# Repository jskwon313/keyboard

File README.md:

# keyboard
This project consists of files that have been used in order to design a keyboard pcb that can be used with mechancial keyboard switches.

The following resources were used:

1) https://github.com/ruiqimao/keyboard-pcb-guide
2) https://i.imgur.com/LQXco3J.png
3) http://www.issi.com/WW/pdf/31FL3731.pdf

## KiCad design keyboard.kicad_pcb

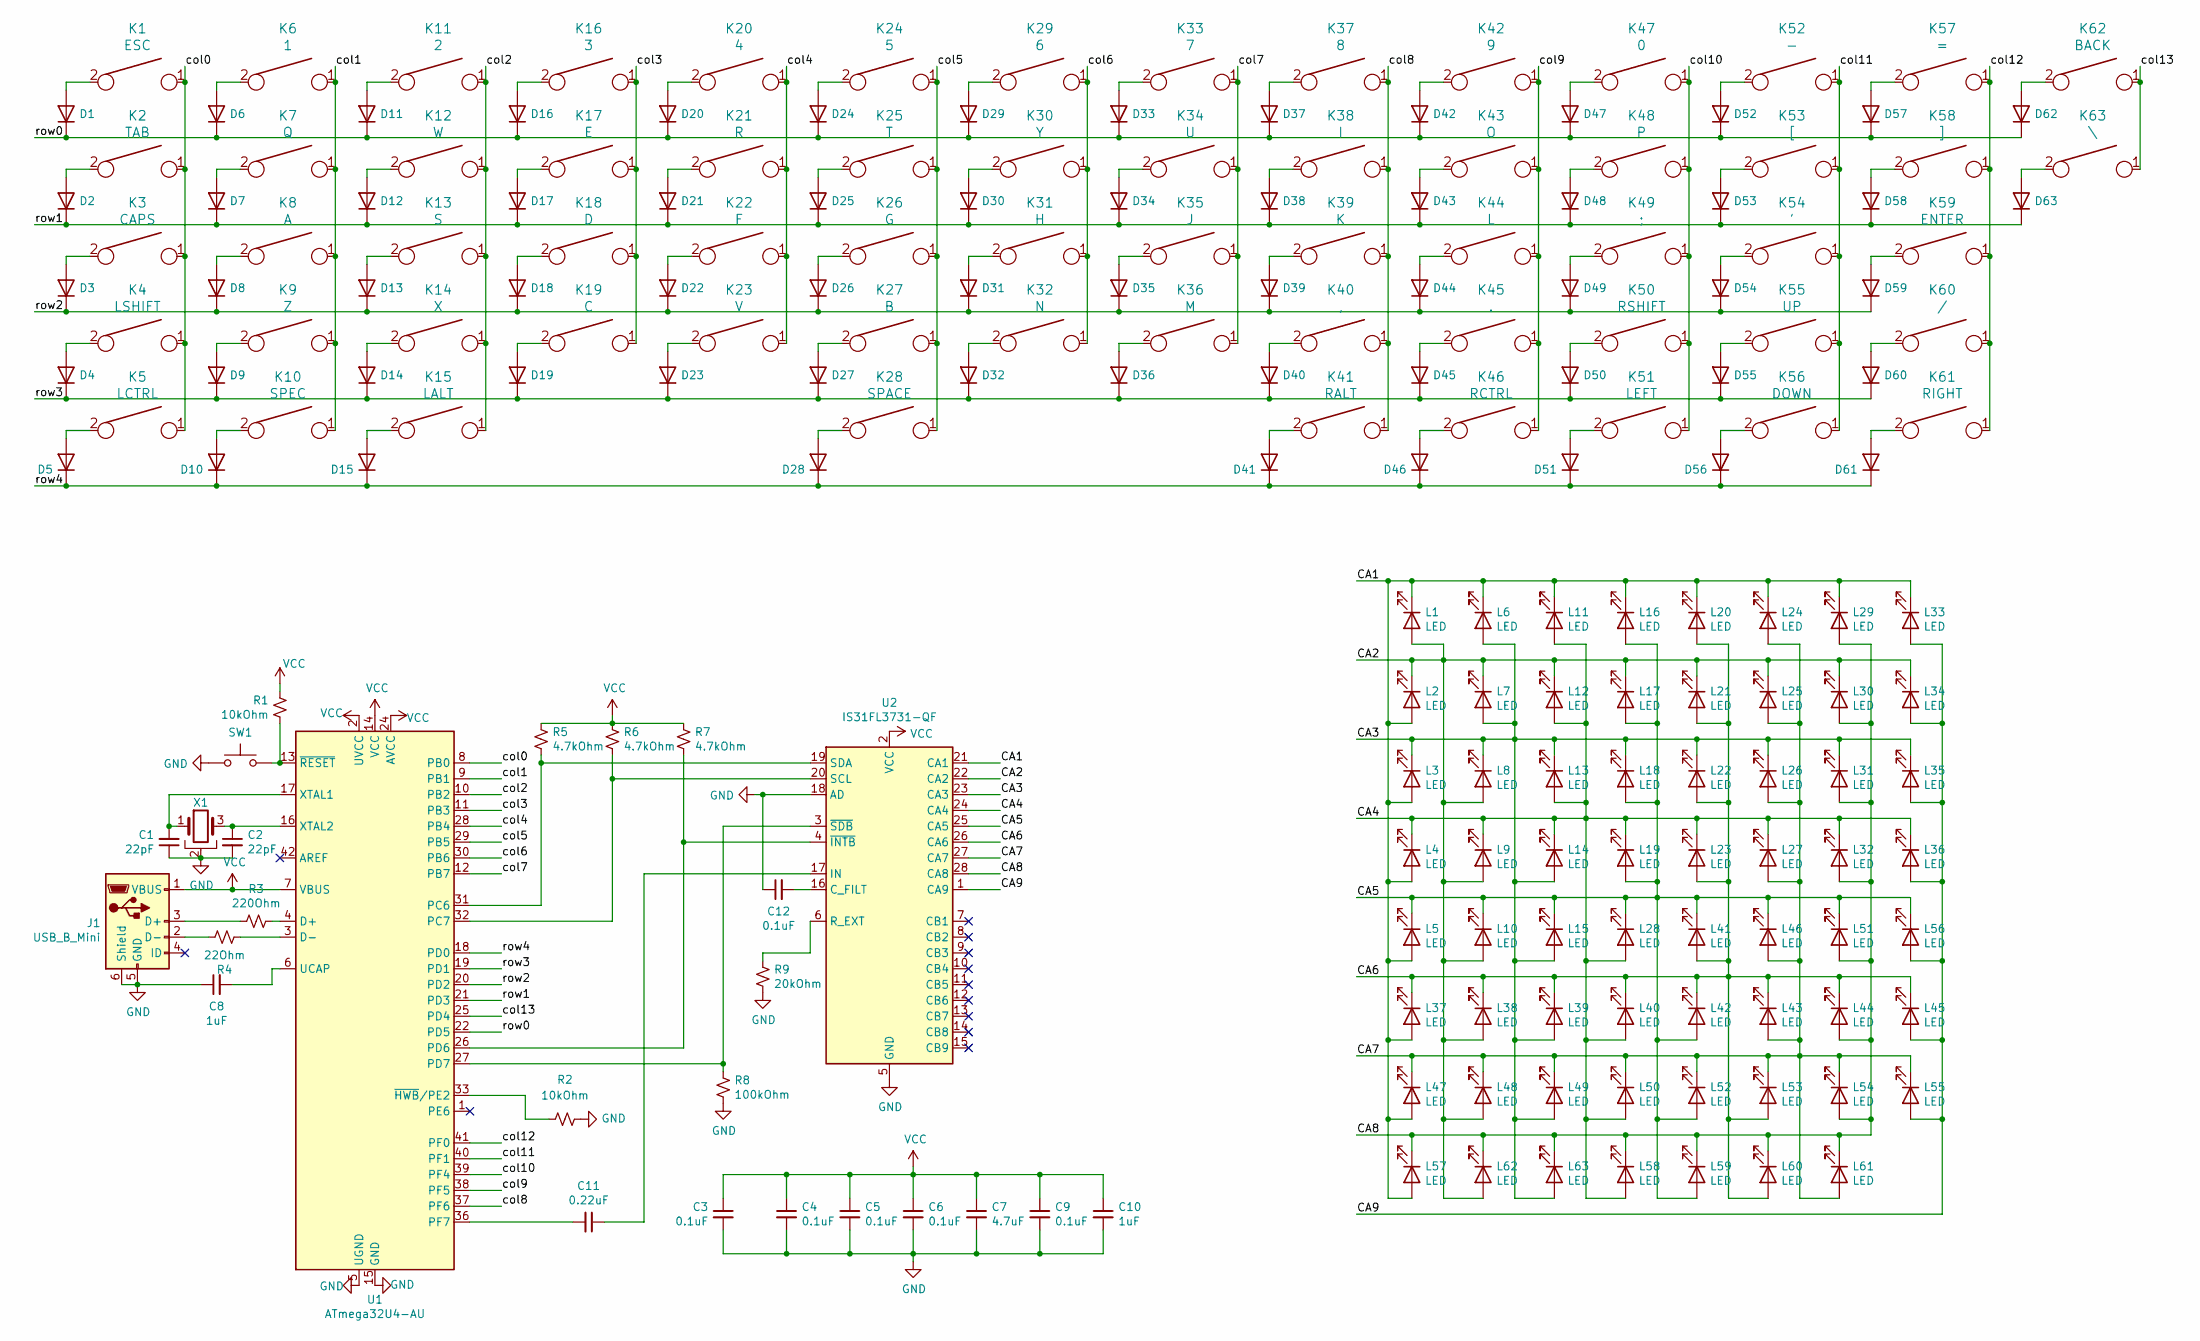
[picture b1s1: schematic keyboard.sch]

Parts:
C1, C2: 22pF; C_0805_2012Metric_Pad1.15x1.40mm_HandSolder
C3, C4, C5, C6, C9, C12: 0.1uF; C_0805_2012Metric_Pad1.15x1.40mm_HandSolder
C7: 4.7uF; C_0805_2012Metric_Pad1.15x1.40mm_HandSolder
C8, C10: 1uF; C_0805_2012Metric_Pad1.15x1.40mm_HandSolder
C11: 0.22uF; C_0805_2012Metric_Pad1.15x1.40mm_HandSolder
D1, D2, D3, D4, D5, D6, D7, D8, D9, D10, D11, D12, D13, D14, D15, D16, D17, D18, D19, D20, D21, D22, D23, D24, D25, D26, D27, D28, D29, D30, D31, D32, D33, D34, D35, D36, D37, D38, D39, D40, D41, D42, D43, D44, D45, D46, D47, D48, D49, D50, D51, D52, D53, D54, D55, D56, D57, D58, D59, D60, D61, D62, D63: D; D_SOD123_axial
J1: USB_B_Mini; USB_miniB_hirose_5S8
K1: ESC; Mx_Alps_100
K2: TAB; Mx_Alps_150
K3: CAPS; Mx_Alps_175
K4: LSHIFT; Mx_Alps_225
K5: LCTRL; Mx_Alps_125
K6: 1; Mx_Alps_100
K7: Q; Mx_Alps_100
K8: A; Mx_Alps_100
K9: Z; Mx_Alps_100
K10: SPEC; Mx_Alps_125
K11: 2; Mx_Alps_100
K12: W; Mx_Alps_100
K13: S; Mx_Alps_100
K14: X; Mx_Alps_100
K15: LALT; Mx_Alps_125
K16: 3; Mx_Alps_100
K17: E; Mx_Alps_100
K18: D; Mx_Alps_100
K19: C; Mx_Alps_100
K20: 4; Mx_Alps_100
K21: R; Mx_Alps_100
K22: F; Mx_Alps_100
K23: V; Mx_Alps_100
K24: 5; Mx_Alps_100
K25: T; Mx_Alps_100
K26: G; Mx_Alps_100
K27: B; Mx_Alps_100
K28: SPACE; Mx_Alps_625
K29: 6; Mx_Alps_100
K30: Y; Mx_Alps_100
K31: H; Mx_Alps_100
K32: N; Mx_Alps_100
K33: 7; Mx_Alps_100
K34: U; Mx_Alps_100
K35: J; Mx_Alps_100
K36: M; Mx_Alps_100
K37: 8; Mx_Alps_100
K38: I; Mx_Alps_100
K39: K; Mx_Alps_100
K40: ,; Mx_Alps_100
K41: RALT; Mx_Alps_100
K42: 9; Mx_Alps_100
K43: O; Mx_Alps_100
K44: L; Mx_Alps_100
K45: .; Mx_Alps_100
K46: RCTRL; Mx_Alps_100
K47: 0; Mx_Alps_100
K48: P; Mx_Alps_100
K49: ;; Mx_Alps_100
K50: RSHIFT; Mx_Alps_175
K51: LEFT; Mx_Alps_100
K52: -; Mx_Alps_100
K53: [; Mx_Alps_100
K54: '; Mx_Alps_100
K55: UP; Mx_Alps_100
K56: DOWN; Mx_Alps_100
K57: =; Mx_Alps_100
K58: ]; Mx_Alps_100
K59: ENTER; Mx_Alps_225
K60: /; Mx_Alps_100
K61: RIGHT; Mx_Alps_100
K62: BACK; Mx_Alps_200
K63: \\; Mx_Alps_150
L1, L2, L3, L4, L5, L6, L7, L8, L9, L10, L11, L12, L13, L14, L15, L16, L17, L18, L19, L20, L21, L22, L23, L24, L25, L26, L27, L28, L29, L30, L31, L32, L33, L34, L35, L36, L37, L38, L39, L40, L41, L42, L43, L44, L45, L46, L47, L48, L49, L50, L51, L52, L53, L54, L55, L56, L57, L58, L59, L60, L61, L62, L63: LED; LED_0603_1608Metric_Pad1.05x0.95mm_HandSolder
R1, R2: 10kOhm; R_0805_2012Metric_Pad1.15x1.40mm_HandSolder
R3: 220Ohm; R_0805_2012Metric_Pad1.15x1.40mm_HandSolder
R4: 22Ohm; R_0805_2012Metric_Pad1.15x1.40mm_HandSolder
R5, R6, R7: 4.7kOhm; R_0805_2012Metric_Pad1.15x1.40mm_HandSolder
R8: 100kOhm; R_0805_2012Metric_Pad1.15x1.40mm_HandSolder
R9: 20kOhm; R_0805_2012Metric_Pad1.15x1.40mm_HandSolder
SW1: SW_Push; SW_SPST_TL3342
U1: ATmega32U4-AU; TQFP-44_10x10mm_P0.8mm
U2: IS31FL3731-QF; QFN-28-1EP_4x4mm_P0.4mm_EP2.3x2.3mm
X1: XTAL_GND; Crystal_SMD_SeikoEpson_FA238-4Pin_3.2x2.5mm_HandSoldering

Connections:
/CA1: L1.1 (K), L2.2 (A), L3.2 (A), L4.2 (A), L5.2 (A), L6.1 (K), L11.1 (K), L16.1 (K), L20.1 (K), L24.1 (K), L29.1 (K), L33.1 (K), L37.2 (A), L47.2 (A), L57.2 (A), U2.21 (CA1)
/CA2: L1.2 (A), L2.1 (K), L7.1 (K), L8.2 (A), L9.2 (A), L10.2 (A), L12.1 (K), L17.1 (K), L21.1 (K), L25.1 (K), L30.1 (K), L34.1 (K), L38.2 (A), L48.2 (A), L62.2 (A), U2.22 (CA2)
/CA3: L3.1 (K), L6.2 (A), L7.2 (A), L8.1 (K), L13.1 (K), L14.2 (A), L15.2 (A), L18.1 (K), L22.1 (K), L26.1 (K), L31.1 (K), L35.1 (K), L39.2 (A), L49.2 (A), L63.2 (A), U2.23 (CA3)
/CA4: L4.1 (K), L9.1 (K), L11.2 (A), L12.2 (A), L13.2 (A), L14.1 (K), L19.1 (K), L23.1 (K), L27.1 (K), L28.2 (A), L32.1 (K), L36.1 (K), L40.2 (A), L50.2 (A), L58.2 (A), U2.24 (CA4)
/CA5: L5.1 (K), L10.1 (K), L15.1 (K), L16.2 (A), L17.2 (A), L18.2 (A), L19.2 (A), L28.1 (K), L41.1 (K), L42.2 (A), L46.1 (K), L51.1 (K), L52.2 (A), L56.1 (K), L59.2 (A), U2.25 (CA5)
/CA6: L20.2 (A), L21.2 (A), L22.2 (A), L23.2 (A), L37.1 (K), L38.1 (K), L39.1 (K), L40.1 (K), L41.2 (A), L42.1 (K), L43.1 (K), L44.1 (K), L45.1 (K), L53.2 (A), L60.2 (A), U2.26 (CA6)
/CA7: L24.2 (A), L25.2 (A), L26.2 (A), L27.2 (A), L43.2 (A), L46.2 (A), L47.1 (K), L48.1 (K), L49.1 (K), L50.1 (K), L52.1 (K), L53.1 (K), L54.1 (K), L55.1 (K), L61.2 (A), U2.27 (CA7)
/CA8: L29.2 (A), L30.2 (A), L31.2 (A), L32.2 (A), L44.2 (A), L51.2 (A), L54.2 (A), L57.1 (K), L58.1 (K), L59.1 (K), L60.1 (K), L61.1 (K), L62.1 (K), L63.1 (K), U2.28 (CA8)
/CA9: L33.2 (A), L34.2 (A), L35.2 (A), L36.2 (A), L45.2 (A), L55.2 (A), L56.2 (A), U2.1 (CA9)
/col0: K1.1, K2.1, K3.1, K4.1, K5.1, U1.8 (PB0)
/col1: K6.1, K7.1, K8.1, K9.1, K10.1, U1.9 (PB1)
/col2: K11.1, K12.1, K13.1, K14.1, K15.1, U1.10 (PB2)
/col3: K16.1, K17.1, K18.1, K19.1, U1.11 (PB3)
/col4: K20.1, K21.1, K22.1, K23.1, U1.28 (PB4)
/col5: K24.1, K25.1, K26.1, K27.1, K28.1, U1.29 (PB5)
/col6: K29.1, K30.1, K31.1, K32.1, U1.30 (PB6)
/col7: K33.1, K34.1, K35.1, K36.1, U1.12 (PB7)
/col8: K37.1, K38.1, K39.1, K40.1, K41.1, U1.37 (PF6)
/col9: K42.1, K43.1, K44.1, K45.1, K46.1, U1.38 (PF5)
/col10: K47.1, K48.1, K49.1, K50.1, K51.1, U1.39 (PF4)
/col11: K52.1, K53.1, K54.1, K55.1, K56.1, U1.40 (PF1)
/col12: K57.1, K58.1, K59.1, K60.1, K61.1, U1.41 (PF0)
/col13: K62.1, K63.1, U1.25 (PD4)
/row0: D1.1 (K), D6.1 (K), D11.1 (K), D16.1 (K), D20.1 (K), D24.1 (K), D29.1 (K), D33.1 (K), D37.1 (K), D42.1 (K), D47.1 (K), D52.1 (K), D57.1 (K), D62.1 (K), U1.22 (PD5)
/row1: D2.1 (K), D7.1 (K), D12.1 (K), D17.1 (K), D21.1 (K), D25.1 (K), D30.1 (K), D34.1 (K), D38.1 (K), D43.1 (K), D48.1 (K), D53.1 (K), D58.1 (K), D63.1 (K), U1.21 (PD3)
/row2: D3.1 (K), D8.1 (K), D13.1 (K), D18.1 (K), D22.1 (K), D26.1 (K), D31.1 (K), D35.1 (K), D39.1 (K), D44.1 (K), D49.1 (K), D54.1 (K), D59.1 (K), U1.20 (PD2)
/row3: D4.1 (K), D9.1 (K), D14.1 (K), D19.1 (K), D23.1 (K), D27.1 (K), D32.1 (K), D36.1 (K), D40.1 (K), D45.1 (K), D50.1 (K), D55.1 (K), D60.1 (K), U1.19 (PD1)
/row4: D5.1 (K), D10.1 (K), D15.1 (K), D28.1 (K), D41.1 (K), D46.1 (K), D51.1 (K), D56.1 (K), D61.1 (K), U1.18 (PD0)
GND: C1.1, C2.2, C3.2, C4.2, C5.2, C6.2, C7.2, C8.1, C9.2, C10.2, C12.1, J1.5 (GND), J1.6 (Shield), R2.2, R8.2, R9.2, SW1.1, U1.5 (UGND), U1.15 (GND), U1.23 (GND), U1.35 (GND), U1.43 (GND), U2.5 (GND), U2.18 (AD), U2.29 (GND), X1.2
unnamed: C1.2, U1.17 (XTAL1), X1.1
unnamed: C2.1, U1.16 (XTAL2), X1.3
unnamed: C8.2, U1.6 (UCAP)
unnamed: C11.1, U2.17 (IN)
unnamed: C11.2, U1.36 (PF7)
unnamed: C12.2, U2.16 (C_FILT)
unnamed: D1.2 (A), K1.2
unnamed: D2.2 (A), K2.2
unnamed: D3.2 (A), K3.2
unnamed: D4.2 (A), K4.2
unnamed: D5.2 (A), K5.2
unnamed: D6.2 (A), K6.2
unnamed: D7.2 (A), K7.2
unnamed: D8.2 (A), K8.2
unnamed: D9.2 (A), K9.2
unnamed: D10.2 (A), K10.2
unnamed: D11.2 (A), K11.2
unnamed: D12.2 (A), K12.2
unnamed: D13.2 (A), K13.2
unnamed: D14.2 (A), K14.2
unnamed: D15.2 (A), K15.2
unnamed: D16.2 (A), K16.2
unnamed: D17.2 (A), K17.2
unnamed: D18.2 (A), K18.2
unnamed: D19.2 (A), K19.2
unnamed: D20.2 (A), K20.2
unnamed: D21.2 (A), K21.2
unnamed: D22.2 (A), K22.2
unnamed: D23.2 (A), K23.2
unnamed: D24.2 (A), K24.2
unnamed: D25.2 (A), K25.2
unnamed: D26.2 (A), K26.2
unnamed: D27.2 (A), K27.2
unnamed: D28.2 (A), K28.2
unnamed: D29.2 (A), K29.2
unnamed: D30.2 (A), K30.2
unnamed: D31.2 (A), K31.2
unnamed: D32.2 (A), K32.2
unnamed: D33.2 (A), K33.2
unnamed: D34.2 (A), K34.2
unnamed: D35.2 (A), K35.2
unnamed: D36.2 (A), K36.2
unnamed: D37.2 (A), K37.2
unnamed: D38.2 (A), K38.2
unnamed: D39.2 (A), K39.2
unnamed: D40.2 (A), K40.2
unnamed: D41.2 (A), K41.2
unnamed: D42.2 (A), K42.2
unnamed: D43.2 (A), K43.2
unnamed: D44.2 (A), K44.2
unnamed: D45.2 (A), K45.2
unnamed: D46.2 (A), K46.2
unnamed: D47.2 (A), K47.2
unnamed: D48.2 (A), K48.2
unnamed: D49.2 (A), K49.2
unnamed: D50.2 (A), K50.2
unnamed: D51.2 (A), K51.2
unnamed: D52.2 (A), K52.2
unnamed: D53.2 (A), K53.2
unnamed: D54.2 (A), K54.2
unnamed: D55.2 (A), K55.2
unnamed: D56.2 (A), K56.2
unnamed: D57.2 (A), K57.2
unnamed: D58.2 (A), K58.2
unnamed: D59.2 (A), K59.2
unnamed: D60.2 (A), K60.2
unnamed: D61.2 (A), K61.2
unnamed: D62.2 (A), K62.2
unnamed: D63.2 (A), K63.2
unnamed: J1.2 (D-), R4.2
unnamed: J1.3 (D+), R3.2
unnamed: R1.2, SW1.2, U1.13 (~RESET)
unnamed: R2.1, U1.33 (~HWB~/PE2)
unnamed: R3.1, U1.4 (D+)
unnamed: R4.1, U1.3 (D-)
unnamed: R5.2, U1.31 (PC6), U2.19 (SDA)
unnamed: R6.2, U1.32 (PC7), U2.20 (SCL)
unnamed: R7.1, U1.26 (PD6), U2.4 (~INTB)
unnamed: R8.1, U1.27 (PD7), U2.3 (~SDB)
unnamed: R9.1, U2.6 (R_EXT)
VCC: C3.1, C4.1, C5.1, C6.1, C7.1, C9.1, C10.1, J1.1 (VBUS), R1.1, R5.1, R6.1, R7.2, U1.2 (UVCC), U1.7 (VBUS), U1.14 (VCC), U1.24 (AVCC), U1.34 (VCC), U1.44 (AVCC), U2.2 (VCC)

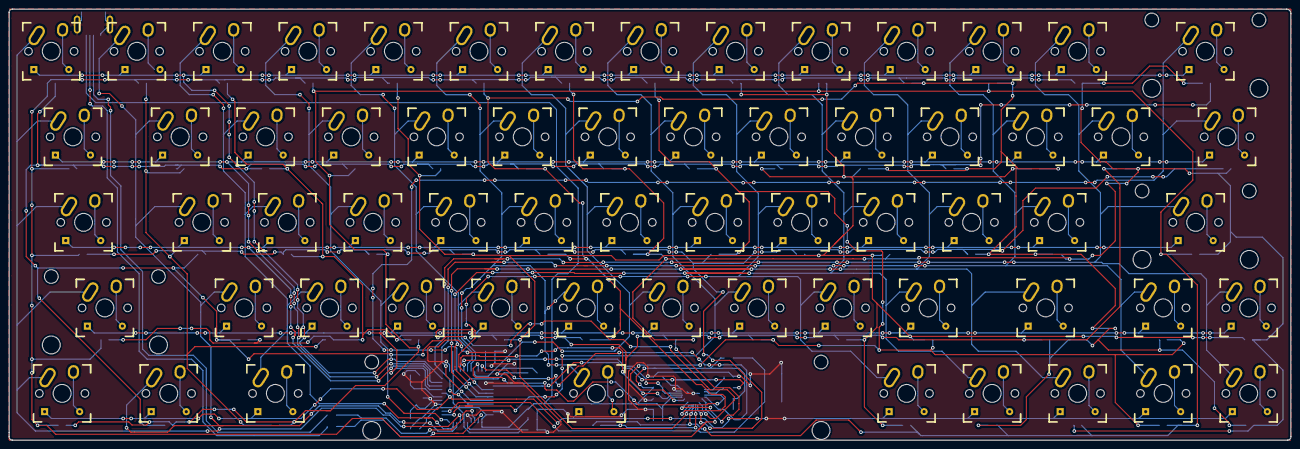
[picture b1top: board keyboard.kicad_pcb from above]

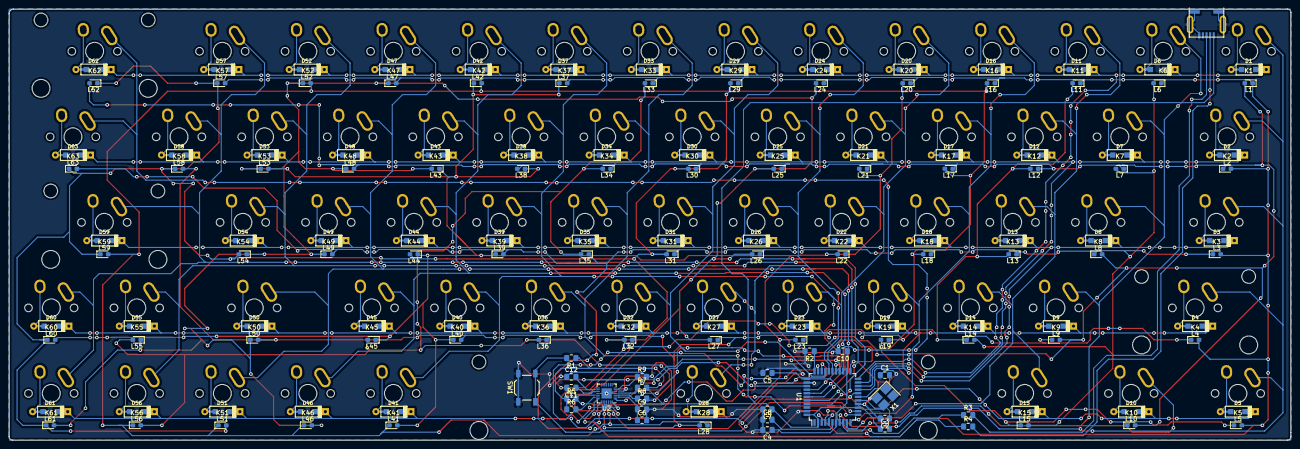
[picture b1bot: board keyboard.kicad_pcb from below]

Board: 2 copper layers, 285.5 x 96.0 mm, 215 parts (152 on the bottom side), 110 nets.

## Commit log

2020-09-07 Initial Push
    Committing the files that I worked on while I had free time. I was able to complete the circuit design and most of the PCB layout.
